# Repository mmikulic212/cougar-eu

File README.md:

# Throttle Cougar Extended Upgrade

Hardware upgrade for ThrustMaster Cougar TQS throttle quadrant.

## Goal

Enable ThrustMaster Cougar throttle to work independently from Cougar stick, with additional switches and encoders. Uses native USB HID - no additional drivers required.

## MMJoy Firmware

This project uses [MMJoy](https://github.com/MMJoy/mmjoy_en) - open-source USB HID joystick firmware for Arduino.

- **Download**: https://github.com/MMJoy/mmjoy_en/releases
- **Wiki**: https://github.com/MMjoy/mmjoy_en/wiki

## MMJoy Configuration Files

Two pre-configured MMJoy settings are included in `mmjoy_setup/`:

### tm_cougar_mlu_32b+hat.mmjoy
- **32 buttons** + hat switch
- 6 axes (throttle, X, Y, rX, rY, Slider)
- CRS (course) controls mapped as **axes**

### tm_cougar_mlu_36b+hat_crs_asbut.mmjoy
- **36 buttons** + hat switch (32 + **4 additional** buttons)
- 6 axes (throttle, X, Y, rX, rY, Slider)
- CRS (course) controls mapped as **buttons** (for target cursor control in simulators)

Both configurations work identically. Choose 36-button version if you want to control target cursor with buttons instead of axes.

## Hardware

### Required Components

| Component | Description | Example |
|-----------|-------------|---------|
| ThrustMaster Cougar TQS | Original throttle quadrant | N/A |
| Custom PCB | Interface board | Order package in `order/` |
| Arduino Pro Micro | USB HID controller (ATmega 32u4) | Generic clone, 5V/16MHz, USB-C version is recommended |
| 1x 2x8-pin connector | For throttle button matrix | 2x8-pin connector |

### Optional Components

| Component | Description | Example |
|-----------|-------------|---------|
| 3x 74HC165 | 8-bit shift register | SN74HC165N DIP-16 |
| 9x Toggle Switch | (ON)-OFF-(ON) DPDT | RS PRO 206-6978 |
| 2x Rotary Encoder | KY-040 with push button | KY-040 module |
| 1x 24-pin DIP socket | For Arduino Pro Micro | |
| 3x 16-pin DIP socket | For 74HC165 | 16-pin DIP socket |
| 3x 10-pin connector | For additional buttons (2x5 IDC header) | 10-pin connector |
| Ribbon cable | 10-pin flat cable | or other cables |

### Recomendation

Orignal throttle and other axis potenciometers can stay and work very wel. But I strongly recommend upgrade to Hall sensors. Unfortunatelly this is still  WIP from my side.

## Wiring and Pinout

### Assembly Images

*Internal view showing PCB, Arduino Pro Micro, shift registers, and wiring*

*Close-up of Arduino Pro Micro installed in socket with connected wires*

*Front view of completed throttle with toggle switches*

*Side view showing throttle grip and switch placement*

The custom PCB can be ordered from any PCB manufacturer (JLCPCB, PCBWay, Seeed, etc.) using Gerber files in `order/` folder.

**No electrical modifications to Cougar throttle are required** - simply connect the custom PCB onto Cougar PCB 2x8 DIP connector and connect via USB.

## Getting Started

1. **Order PCB** - Download Gerber files from `order/` folder
2. **Assemble** - Solder components, install Arduino and shift registers in sockets, connect to throttle
3. **Flash firmware** - Upload MMJoy to Arduino Pro Micro ([see MMJoy Wiki](https://github.com/MMjoy/mmjoy_en/wiki/Firmware-upload))
4. **Configure** - Use MMJoy configurator to set up inputs/outputs. Load configuration from `mmjoy_setup/` and modify based on your wiring
5. **Test** - Verify all buttons, encoders, and axes work correctly

## Project Structure

| Folder | Description |
|--------|-------------|
| `board/` | PCB design files (Eagle) |
| `mmjoy_setup/` | MMJoy configuration files |
| `order/` | Gerber files for PCB manufacturing |
| `references/` | Reference documentation |

## License

CC BY-NC-SA 4.0 - Non-commercial use only, share-alike

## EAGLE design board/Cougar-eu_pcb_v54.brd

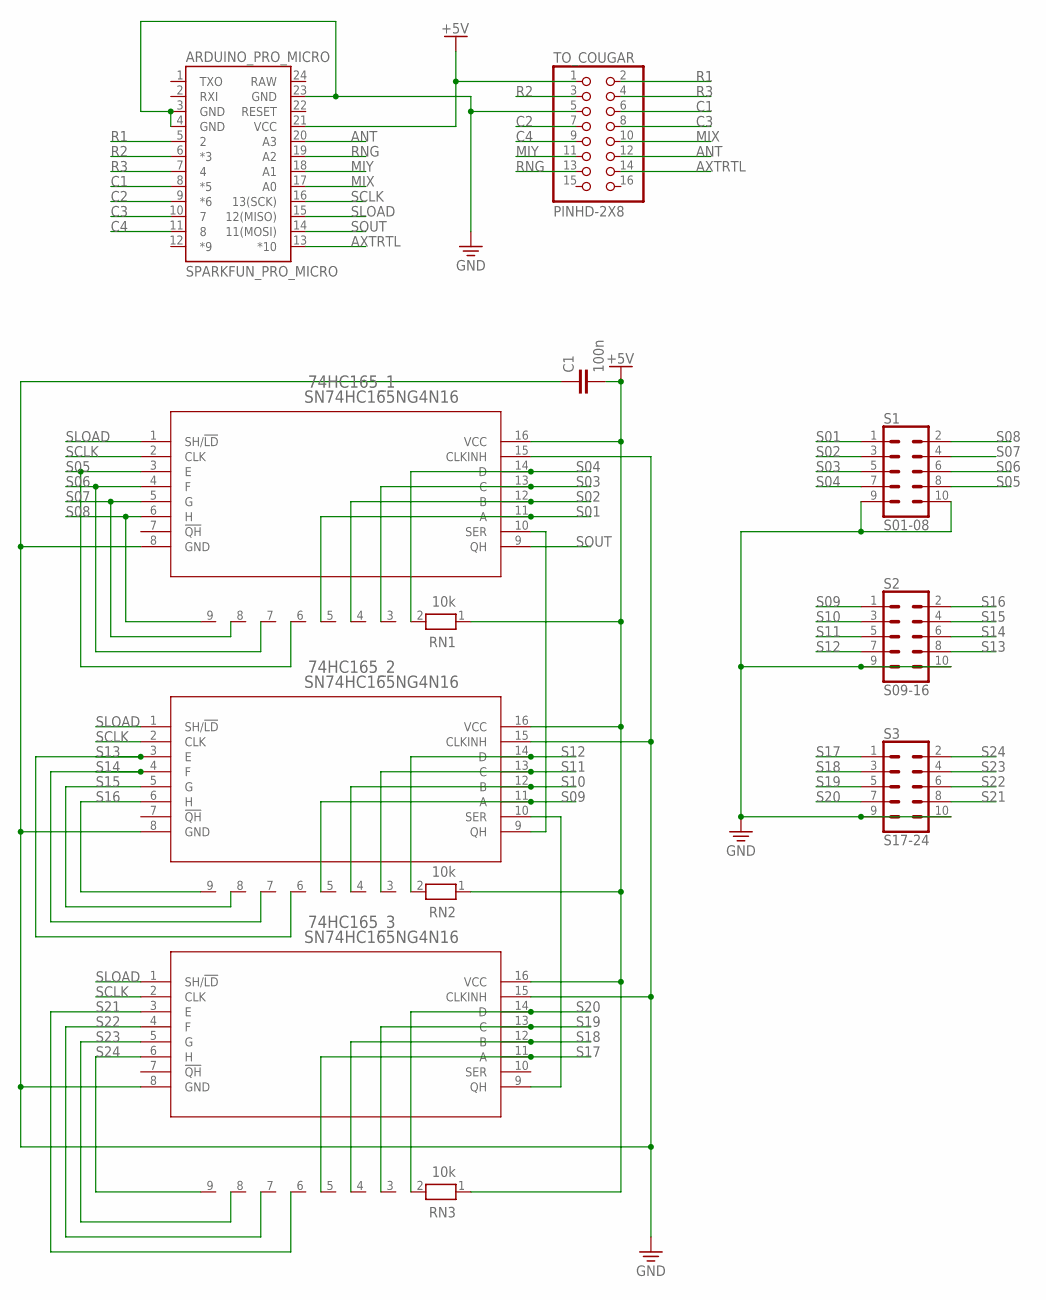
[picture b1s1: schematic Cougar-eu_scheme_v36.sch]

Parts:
74HC165_1, 74HC165_2, 74HC165_3: SN74HC165NG4N16; N16
ARDUINO_PRO_MICRO: SPARKFUN_PRO_MICRO
C1: 100n; C2.5-3
RN1, RN2, RN3: 10k; RN-9
S1: S01-08; 2X5
S2: S09-16; 2X5
S3: S17-24; 2X5
TO_COUGAR: PINHD-2X8; 2X08

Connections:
+5V: 74HC165_1.16 (VCC), 74HC165_2.16 (VCC), 74HC165_3.16 (VCC), ARDUINO_PRO_MICRO.21 (VCC), C1.2, RN1.1, RN2.1, RN3.1, TO_COUGAR.1
ANT: ARDUINO_PRO_MICRO.20 (A3), TO_COUGAR.12
AXTRTL: ARDUINO_PRO_MICRO.13 (*10), TO_COUGAR.14
C1: ARDUINO_PRO_MICRO.8 (*5), TO_COUGAR.6
C2: ARDUINO_PRO_MICRO.9 (*6), TO_COUGAR.7
C3: ARDUINO_PRO_MICRO.10 (7), TO_COUGAR.8
C4: ARDUINO_PRO_MICRO.11 (8), TO_COUGAR.9
GND: 74HC165_1.8 (GND), 74HC165_1.15 (CLKINH), 74HC165_2.8 (GND), 74HC165_2.15 (CLKINH), 74HC165_3.8 (GND), 74HC165_3.15 (CLKINH), ARDUINO_PRO_MICRO.3 (GND), ARDUINO_PRO_MICRO.4 (GND), ARDUINO_PRO_MICRO.23 (GND), C1.1, S1.9, S1.10, S2.9, S2.10, S3.9, S3.10, TO_COUGAR.5
MIX: ARDUINO_PRO_MICRO.17 (A0), TO_COUGAR.10
MIY: ARDUINO_PRO_MICRO.18 (A1), TO_COUGAR.11
unnamed: 74HC165_1.10 (SER), 74HC165_2.9 (QH)
unnamed: 74HC165_2.10 (SER), 74HC165_3.9 (QH)
R1: ARDUINO_PRO_MICRO.5 (2), TO_COUGAR.2
R2: ARDUINO_PRO_MICRO.6 (*3), TO_COUGAR.3
R3: ARDUINO_PRO_MICRO.7 (4), TO_COUGAR.4
RAW: ARDUINO_PRO_MICRO.24 (RAW)
RNG: ARDUINO_PRO_MICRO.19 (A2), TO_COUGAR.13
S01: 74HC165_1.11 (A), RN1.5, S1.1
S02: 74HC165_1.12 (B), RN1.4, S1.3
S03: 74HC165_1.13 (C), RN1.3, S1.5
S04: 74HC165_1.14 (D), RN1.2, S1.7
S05: 74HC165_1.3 (E), RN1.6, S1.8
S06: 74HC165_1.4 (F), RN1.7, S1.6
S07: 74HC165_1.5 (G), RN1.8, S1.4
S08: 74HC165_1.6 (H), RN1.9, S1.2
S09: 74HC165_2.11 (A), RN2.5, S2.1
S10: 74HC165_2.12 (B), RN2.4, S2.3
S11: 74HC165_2.13 (C), RN2.3, S2.5
S12: 74HC165_2.14 (D), RN2.2, S2.7
S13: 74HC165_2.3 (E), RN2.6, S2.8
S14: 74HC165_2.4 (F), RN2.7, S2.6
S15: 74HC165_2.5 (G), RN2.8, S2.4
S16: 74HC165_2.6 (H), RN2.9, S2.2
S17: 74HC165_3.11 (A), RN3.5, S3.1
S18: 74HC165_3.12 (B), RN3.4, S3.3
S19: 74HC165_3.13 (C), RN3.3, S3.5
S20: 74HC165_3.14 (D), RN3.2, S3.7
S21: 74HC165_3.3 (E), RN3.6, S3.8
S22: 74HC165_3.4 (F), RN3.7, S3.6
S23: 74HC165_3.5 (G), RN3.8, S3.4
S24: 74HC165_3.6 (H), RN3.9, S3.2
SCLK: 74HC165_1.2 (CLK), 74HC165_2.2 (CLK), 74HC165_3.2 (CLK), ARDUINO_PRO_MICRO.16 (13(SCK))
SLOAD: 74HC165_1.1 (SH/!LD), 74HC165_2.1 (SH/!LD), 74HC165_3.1 (SH/!LD), ARDUINO_PRO_MICRO.15 (12(MISO))
SOUT: 74HC165_1.9 (QH), ARDUINO_PRO_MICRO.14 (11(MOSI))

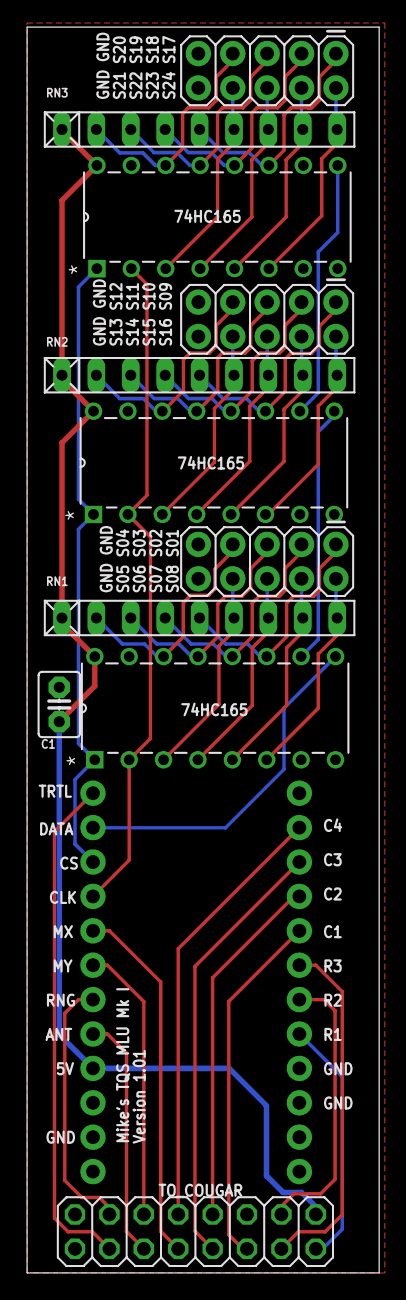
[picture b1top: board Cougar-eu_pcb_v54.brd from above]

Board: 2 copper layers, 26.0 x 92.0 mm, 12 parts (0 on the bottom side), 43 nets.

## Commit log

2024-07-18 add board
2026-02-14 Add comprehensive README with MMJoy firmware guide, hardware components table, and assembly images
    - Rewrote README with detailed project description
    - Added MMJoy firmware section with download/wiki links
    - Added hardware components tables (required + optional)
    - Added PCB ordering info (any manufacturer)
    - Added Getting Started guide (Order → Assemble → Flash → Configure → Test)
    - Added assembly images with descriptions
2026-02-14 additional info
2026-02-14 Fix cougar_button_setup.jpg - convert from HEIF to proper JPEG
2026-02-14 Add MMJoy configuration files description to README

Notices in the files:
parts and their libraries:
SparkFun-Boards: Licensing: Creative Commons ShareAlike 4.0 International - https://creativecommons.org/licenses/by-sa/4.0
COPYRIGHT: Copyright (C) 2022 Ultra Librarian. All rights reserved.
